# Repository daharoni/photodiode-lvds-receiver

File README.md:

# Photodiode LVDS Receiver

Optical receiver module for the next-generation wireless UCLA Miniscope data
uplink. It succeeds the receiver used with the Miniscope Zero link
(bioRxiv 10.64898/2026.09.05.745822). Target: 50 Mbps line rate (8b/10b,
40 Mbps payload, UI = 20 ns).

Signal chain: silicon APD (primary Hamamatsu S12023-10; FDS010 PIN only as a bench
fallback) on a programmable, temperature-compensated 100-220 V bias
(APD_BIAS) -> OPA857 transimpedance
amplifier -> AC coupling -> OPA855 fixed-gain post-amplifier -> TLV3605
comparator sliced at the AC baseline, LVDS output -> one LVDS pair to an ECP5
FPGA (ULX3S first), which does clock recovery, 8b/10b decode and redundant-lane
merging. An on-module ESP32-C6 trims the APD bias and TIA gain slowly over a
CAN link and reports the module identity. The architecture is analog-first by
decision; see `docs/decision-log.md` (entries 11 and 12).

Each module has one 24-pin USB-C receptacle (decision 14) that carries 5 V, the LVDS
pair duplicated on both SuperSpeed TX pairs, CAN on both RX pairs and USB D+/D- for
programming and self-test from a laptop with no FPGA attached; a scope header and
test points serve the bench. It is intended for a shielded aluminum housing with a
swappable optical bandpass filter.

## Status

Pre-G1, layout in progress (2026-10-12). Rev A schematic is complete (six
hierarchical sheets, 221 components, 144 nets, ERC 0 errors / 0 warnings, spec
revision 4 after decision 14); the generators are frozen and edits go through the
KiCad GUI. The PCB is a 6-layer JLCPCB JLC06161H-3313 board on a 75 x 50 mm
placeholder outline with all 221 footprints placed by the first-pass placement
script; routing is complete (0 unconnected, DRC 11 items accepted in writing in the review README). No hardware, no measurements; three ngspice simulations
with TI models exist (`docs/simulation/README.md`, SIMULATED, not VERIFIED).
Component choices are provisional until the bring-up gates in
`docs/bringup/gates.md` pass. The largest open risks are the APD bias supply, the
USB-C cable and foreign-host behaviour (decision 14), OPA857 behavior at 6 pF,
post-amp clipping and comparator noise at small overdrive, and the firmware
range-control loop. Per-sheet as-built notes with datasheet citations are in
`docs/schematic/`; `docs/receiver-guide.html` is the derived field guide.

## Repo map

| Path | Contents |
|---|---|
| `docs/requirements.md` | Requirements, user answers, open items |
| `docs/architecture.md` | Block-by-block design and reasoning |
| `docs/decision-log.md` | Dated decisions and standing corrections |
| `docs/bringup/gates.md` | Gates G1-G4 and checklists |
| `docs/research/` | Component research; `downloads/` is raw untrusted input |
| `docs/datasheets/` | Datasheets |
| `docs/calculations/` | Design calculations |
| `docs/schematic/` | Rev A sheet specs, per-sheet as-built notes, `overview.html` parts and pinout page |
| `docs/pcb/` | JLCPCB fabrication settings, J50 receptacle DFM note, placement plan |
| `docs/simulation/` | ngspice simulations (OPA855, OPA857 at 6 pF, VCM_REF buffer) |
| `docs/firmware/` | CAN and USB console protocol |
| `docs/receiver-guide.html` | Self-contained field guide derived from the docs above (regenerate when they change) |
| `hardware/pcb/` | KiCad project (`receiver-module/`) |
| `hardware/mechanical/` | Enclosure and filter holder (TBD) |
| `firmware/` | ECP5 gateware; ESP32-C6 module firmware (TBD) |
| `tools/` | Helper scripts |
| `CLAUDE.md` | Guide for Claude Code sessions |

## Opening the KiCad project

Requires KiCad 10 and the lab component library from
`~/Projects/kicad-lab-library`, installed with that repo's install script so
that `${AHARONI_LAB_KICAD_LIB}` resolves. Then open
`hardware/pcb/receiver-module/receiver-module.kicad_pro`. The sheets were
generated by the scripts in `hardware/pcb/receiver-module/gen/` using
`tools/kicad_sch`; the generators are frozen since 2026-10-09 (`gen/FROZEN`,
layout started), so schematic changes go through the KiCad GUI with the spec and
as-built notes in `docs/schematic/` updated by hand.
New parts are added to the lab library by PR, not as project-local symbols.

## Documents to read first

1. `docs/requirements.md`
2. `docs/architecture.md`
3. `docs/decision-log.md`
4. `docs/bringup/gates.md`
5. `docs/receiver-guide.html` (derived overview; open in a browser)

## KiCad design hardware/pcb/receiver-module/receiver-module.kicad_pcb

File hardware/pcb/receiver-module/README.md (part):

# receiver-module (KiCad 10 project, Rev A schematic)

Photodiode LVDS Receiver, Rev A0, Aharoni Lab, UCLA.

**Nothing in this project is fabrication-approved.** The six hierarchical sheets are populated
with lab-library parts, values and footprints per `docs/schematic/rev-a-sheet-specs.md`; project ERC on the root
reports 0 errors and 0 warnings (kicad-cli 10.0.5, 2026-10-09, revision 4 after decision 14). The netlist had 223 components on that date; since 2026-10-22 it has 221 (C181 and R170 removed, Connector 33 -> 31; Power 79, Controller 55, Connector 31 including mounting holes H1-H4 added 2026-10-09, Front End 26, Slicer 17, Monitor 13) on 144 nets. The PCB carries all 221 footprints (H1-H4 included), placed by the first-pass placement script and since hand-placed and fully routed (see Board below). H1-H4 need lab-library PR #62 (branch `add-mounting-holes`, symbol and footprint `MountingHole_2.2mm_M2_Pad_Via`) merged or checked out so the symbol resolves. The S12023 pinout fix (lab-library PR #63) is merged into main. U6 (TLV431, decision 23) needs lab-library branch `add-tlv431` checked out or merged. Status labels used
in notes: VERIFIED / PROPOSED / UNRESOLVED.

## Generated sheets

**FROZEN since 2026-10-09 (PCB layout started).** The generators exit with status 2 while `gen/FROZEN` exists, because regeneration would rewrite the `.kicad_sch` files with new UUIDs and break the schematic-to-board link. Schematic changes now go through the KiCad GUI, with the spec and as-built docs updated by hand. To unfreeze, see `gen/FROZEN` (delete it deliberately, regenerate all sheets in order, re-import to the PCB, re-annotate/re-link footprints). The text below is historical until then.

Each sub-sheet and the root are produced by `gen/<sheet>.py` using the `tools/kicad_sch` package
(`cd tools && python3 gen/...` from the project root; see `tools/kicad_sch/README.md`). Regenerate in
the order power, frontend, slicer, control, connector, controller, root. Each sheet keeps its uuid, so
instance paths stay stable. KiCad's bundled `power:PWR_FLAG` / `power:GND` symbols are used alongside
the lab library. Reference designator ranges per sheet are listed in the spec document.

Validation: `kicad-cli sch erc` and `kicad-cli sch export netlist` on `receiver-module.kicad_sch`
(kicad-cli path in CLAUDE.md). Revision 4 (decision 14) needs lab-library PR #61 (branch `add-usbc-fanout-efuse-esd`: symbols `AharoniLab_Connector:632723300011`, `AharoniLab_Power:TPS259631DDAR`, `AharoniLab_Interface:SN65LVDS104PW`, `AharoniLab_Misc:TPD6E05U06` and their footprints) to be merged before this project is opened on another machine; the generators embed the library symbols, so regenerate after any library change. Revision 3 parts (AharoniLab_Switch / AharoniLab_Switch_SMD for SW60/SW61, lab-library PR #60) are still used: the global sym-lib-table and fp-lib-table must carry those rows.

## How to open

Open `receiver-module.kicad_pro` in KiCad 10. Symbol and footprint libraries come from the global
tables (the lab library is global via `${AHARONI_LAB_KICAD_LIB}`); this project has no
`sym-lib-table` or `fp-lib-table` on purpose. Project text variables: TITLE, REV, COMPANY.

## Sheets

| File | Purpose |
|---|---|
| `receiver-module.kicad_sch` | Root: hierarchical sheet symbols only, in signal-flow order |
| `power.kicad_sch` | VBUS in, TPS259631 eFuse U5 to the internal +5V rail; 3V3 and 3V3_D rails; LT8365 boost + doubler APD bias (HV_ nets, clamp, stage-1 RC filter) -> APD_BIAS, HV_MON divider, DAC_HV trim input, HV_DIS gate |
| `frontend.kicad_sch` | APD, OPA857 TIA with 20k/5k CTRL, AC coupling, OPA855 x7 post-amp, 68 MHz low-pass, AC coupling to SDET_P (TIA_TAP out, VCM_REF in) |
| `slicer.kicad_sch` | TLV3605 sliced at VCM_REF baseline with DAC_TH trim and ~3 mV hysteresis, LVDS out |
| `control.kicad_sch` | Monitor: OPA2320 VCM_REF 1.65 V buffer and BAS70 RSSI minimum detector from TIA_TAP |
| `connector.kicad_sch` | single 24-pin USB-C J50: VBUS out, USB_DP/USB_DN, CC1_SENSE/CC2_SENSE, AUX (SBU tie), LVDS fan-out U50 to both SuperSpeed TX pairs, CAN on both RX pairs (nets CAN_P/CAN_N (CANH/CANL; renamed from CAN_H/CAN_L 2026-10-16 so the KiCad diff-pair router pairs them)), ESD arrays U51/U52, scope header J51, test points |
| `controller.kicad_sch` | ESP32-C6-MINI-1, MCP4728 DAC, ADS1115 ADC, SN65HVD230 CAN, USBLC6 and 22R D+/D- (USB from the Connector sheet), RESET/BOOT switches, CC1_SENSE/CC2_SENSE inputs on IO4/IO5 |

`GND` is a global net (global label in every sub-sheet). Other power nets are sheet pins. Nets at or above 50 V are prefixed `HV_` and, with `APD_BIAS`, belong to net class `HV` (1.0 mm clearance).

## Board

`receiver-module.kicad_pcb`: 6-layer board (stackup below), 75 x 50 mm placeholder outline on Edge.Cuts, all footprints placed by the first-pass placement script (221 components after the shield RC removal, 2026-10-22; 222 components plus the four mounting holes H1-H4 = 225 footprints since R214 was added, 2026-10-23) (below). Routing has been complete since mid-October 2026: 0 unconnected pads, DRC 11 items (2026-10-25; 44 on 2026-10-23, 48 before: the 32 mounting-hole hole_to_hole items went with the H1-H4 `_Pad` footprint variant and the U20 pin 9 starved thermal with a solid connection; remaining 5 silk_edge, 4 diff_pair_gap, 1 uncoupled, 1 silk_overlap), all accepted in writing in `docs/review/2026-10-22-rev-a-review/README.md`; all vias are epoxy filled and capped at order (decision 30). The file holds 225 footprint entries on 2026-10-23 (222 components plus H1-H4). Rules and fabrication settings follow `docs/pcb/jlcpcb-fab-settings.md` (research, PROPOSED values, nothing measured).

### First-pass placement (2026-10-09, PROPOSED)

`tools/pcb_place.py` (runs under KiCad's bundled Python, which has `pcbnew`) applies `placement/placement-spec.json`: board outline, per-block side and region, fixed anchor parts (ICs, connectors, APD, switches, mounting holes) and a `near` pad target for each passive. Passives are packed on a 0.25 mm grid at the nearest free spot to their target, with courtyard-plus-margin collision checks (0.15 mm, 0.65 mm for HV-class parts, 0.3 mm for HV_LADDER), through-hole parts blocking both sides, an ESP32 antenna keep-out, and region growth when a block is full. Blocks are packed in spec order. Result: 223 placed, 0 courtyard overlaps, 0 clearance violations (kicad-cli DRC); remaining DRC items are silk overlaps (reference labels not yet cleaned up), silk near the edge, and the 32 hole-to-hole hits from the via rings of the `MountingHole_2.2mm_M2_Pad_Via` footprints (0.35 mm between the via holes and the 2.2 mm hole, constraint 0.45 mm; swap H1-H4 to the `_Pad` variant without vias or accept it on the high-precision tier).

Run from this directory, with KiCad closed:

```
PYTHONPATH=../../../tools /Users/daharoni/Applications/KiCad/KiCad.app/Contents/Frameworks/Python.framework/Versions/Current/bin/python3 \
  ../../../tools/pcb_place.py receiver-module.kicad_pcb placement/placement-spec.json --out receiver-module.kicad_pcb --report /tmp/report.json
```

It re-places EVERY footprint from the spec, so do not run it on a board with hand placement you want to keep. Floor plan (y down, optical end left): fast chain on the top centre line (D10 at x 9 mm, OPA857, OPA855, filter, TLV3605, SN65LVDS104, ESD arrays, J50 at the right edge with the mouth overhanging 0.95 mm); HV island along the back edge on top (HV_MON, HV_OUT, FB ladder, LT8365 boost, HV_DIS); J51 at the front left; status LED, test points and the RESET/BOOT switches at the front right. Bottom: ESP32-C6 with its antenna over the front edge (keep-out 41-57 x 44-50 mm, both sides), USB ESD and CAN transceiver under J50, CC dividers and eFuse under the connector end, 3V3/3V3_D regulators and DAC/ADC under the HV island, VCM_REF buffer and RSSI detector under the post-amp. The optical window must be centred on the APD can, which sits 1.27 mm from the D10 footprint origin (pad 1, the anode): to the left of it since the 180-degree rotation of 2026-10-22 (see below). The renders used for review are not committed; `kicad-cli pcb render --side top|bottom` regenerates them.

### Hand placement and HV island rearrangement (2026-10-13, PROPOSED)

Daniel re-placed most of the board by hand after the first pass (commit f10238c). The LT8365 island was then rearranged by script (`tools`-free pcbnew snippet, not kept) on the following plan; coordinates are mm from the board's top-left corner, back edge at y = 0. This was the placement state on 2026-10-13, before routing (routing is now complete); nothing was measured.

- U3 is at (48.3, 9.6), rotation 0, so pins 9-16 are on its right side: SW (14, 16) at the top-right corner, FBX (9) at the bottom-right. Power ground leaves the exposed pad at the EN/SW corners, signal ground at the VC/FBX corners (LT8365 Rev. A p.7 pin descriptions, Figure 5 p.16).
- Switching cell along the back edge, right of L1: L1 above U3 with its SW pad 2.4 mm above pin 16, D1 anode 0.6 mm from the L1 SW pad, then R7 and C5 in a row (C5 GND pad to be stitched to GND1 at the pad). C6 (pump) hangs on the same SW blob below D1; D3, D4, C7, R30 continue to the right; C25 sits under the R30 HV_OUT pad. HV_OUT leaves R30 at x 67.3 and is meant to run up to a 0.3 mm lane along the back edge at y about 1.2 (1.0 mm from the edge), then left to the clamp at R17/Q1. Every pad under that lane was placed with its top edge at y >= 2.5 so the 1.0/1.25 mm HV clearances hold.
- FBX island at pin 9: C22 (SS) and R24 (RT) in a column 1.8 mm right of pins 10/11; R8 (ladder end), R12 (bottom resistor) and C26 directly below-right of pin 9 (FBX pads 1.8 mm from the pin); R14 and R15 one column further; the ladder R9, R10, R11 runs right along y 13-15 to the HV_OUT pad of R11 at (63.2, 14.7), 4 mm below D4. R13/C27 (DAC leg) sit beside R14. SYNC parts R26/R27/TP2 (DNP) are in a row at y 17.9: route them only if fitted. C26 (10 pF, DNP in the schematic) is worth fitting as an FBX noise shunt: PROPOSED, not simulated.
- TH1 (NTC in the FBX bottom leg) moved to (10.0, 30.2) just below the APD can, per docs/calculations/apd-bias-design.md section 7 ("on APD can ground tab / thermal link"); its node is the low-impedance end of R12, so the 45 mm run is acceptable.
- LT8365 low-voltage passives in two columns left of U3 (x 40-45): R22/R23 (EN) at the top, C19/C20 at VIN, C21 at INTVCC, R28/R29 at BIAS, R25/C23/C24 at VC; L2 and C18 further left at y 9.9; RV1 at (31, 10.5). J1 moved to x 70.3 and Q3 to (70.5, 15.8) to clear the HV_OUT riser.
- D2 (DNP, purpose not stated in the datasheet) is parked at (66.0, 17.6) off the SW node; if it is ever fitted it must move onto the SW blob.
- Clamp, monitor, stage-1 filter, APD and the whole fast chain are unchanged. DRC (kicad-cli 10.0.5): no clearance, courtyard or hole violations; only silk overlaps (reference labels not yet cleaned up), silk near the edge, and the 32 known mounting-hole via-ring hits.

Distances after the move (centre to centre): C6 pump cap to C87 19 mm (was 10.5), L1 to U20 22.5 mm (was 17.6), FBX end of the ladder (R8) to U3 pin 9 about 2.5 mm (was 16). The D1-R7-C5 path is about 15 mm of trace; with GND1 0.1 mm below F.Cu the loop area stays small provided C5's GND pad and the U3 pad are via-stitched.

Files for the board:

| File | Purpose |
|---|---|
| `receiver-module.kicad_pcb` | board, stackup, plot parameters (`pcbplotparams`) |
| `receiver-module.kicad_pro` | design-rule constraints, net classes and net-class patterns |
| `receiver-module.kicad_dru` | custom DRC rules: diff-pair gap/uncoupled/skew/keep-out, HV edge and pad clearance, same-footprint HV exception. A syntax error makes KiCad ignore the WHOLE file silently (kicad-cli reports no error), so after editing it confirm a rule is live, e.g. delete the last rule and check that DRC messages change |
| `../../../tools/netclass_membership.py` | prints which nets each class pattern catches (run from the repo root) |

### Second placement pass, copper pours and rule areas (2026-10-14, PROPOSED)

Daniel's second hand pass (commit b9dc777) rebuilt the LT8365 cell with D2 (the GND-to-SW clamp of the LT8365 Rev. A p.30 3 V to 6 V reference circuit; purpose still UNRESOLVED in `docs/schematic/power.md`) on the SW node, regrouped the FBX, DAC and pot legs under U3, moved U1/U4 beside the eFuse and Q3/R33/R34/J1 next to the EN divider. Script changes after it (coordinates in mm from the top-left corner):

- Netclass: `Net-(D1-A)` (SW) and `Net-(D1-K)` (replaced by `Net-(D3-A)` on 2026-10-22, see below) added to HV; C22/R24 moved to (51.85, 11.65)/(51.85, 13.25) to clear the 1.25 mm pad rule.
- Hysteresis network: C87 (100 pF) at (37.0, 21.8) on the input side, 2.75 mm from U20 pin 4; R87 swapped with C83 so R87 sits at (42.0, 20.78) on the output side (LVDS_P pad 4 mm from pin 12) and C83 (VCCO 1 uF) moved to (37.0, 17.15).
- ESP32 U60 moved 6 mm left to (43.0, 38.7) with C191/C192 and the ADS1115 cluster (U63 at (28.75, 46.38), R206/R207/C197/C198/C200 at x 23.8, C195 at (29.0, 48.75), R208/C199/R209 at x 33.75). TP62/TP63/R203/D60 moved out of the antenna end to x 51 to 54, y 36 to 40.
- J51 (debug header) now lies along the front edge at (54.31, 47.6), rotation 90, pins at y 47.6 from x 54.3 to 67.0, 2.9 mm right of the antenna keep-out and clear of H4. The USB-C CC network (C182, C183, R181, R184, R185, R187, R188, R189) that was under it moved to B.Cu columns x 52.5 and 55.5, y 35.0 to 39.8, between the module and U64.
- Zones (all `thermal relief` pad connection, clearance 0.2 mm, min width 0.2 mm, spoke 0.4 mm, gap 0.25 mm, islands removed): `GND_F` (F.Cu), `GND1` (In1.Cu), `GND_In3` (In3.Cu, priority 0), `GND2` (In4.Cu), `GND_B` (B.Cu), each the full outline. Rail pours on In3.Cu with higher priority (reshaped 2026-10-15 against the pad list, PROPOSED): `PWR_3V3` (priority 1: U1-output corner x 54-72, y 1.5-9.5, neck x 52-58.8 down to y 20.4, front-end band x 6-49, y 17.5-31.8), `PWR_3V3_D` (priority 2: x 49.4-72 from y 20.8, so the DAC cluster U62/C194/R192 at x 50.8-51.8 is inside, and the front band x 18-72, y 32.3-49.5), `PWR_5V` (priority 3: U1-input column x 57.5-62.3, y 3.3-18 plus the eFuse/U4-input block x 62.3-72, y 9.9-18; it cuts the 3V3 pour, which keeps a 1.8 mm strip along y 1.5-3.3). Rail pads that stay outside their pour and need a trace: 3V3 TP50; 3V3_D R33 (EN divider), R39 (at J50) and the U4 output group U4.5/C30/C31 (link on B.Cu plus one In2 track down to the 3V3_D pour); +5V C18/L2 (LT8365 input, In2 track from the 5V pour, about 21 mm) and C29. The user's first-pass 3V3/3V3_D/+5V outer-layer tracks can be replaced by vias into these pours. In2.Cu has no pour (signal layer). The three rail zones report `isolated_copper` until their vias exist. U10 pad 17 (OPA857 exposed pad) has a per-pad solid zone connection because the input window below leaves it one spoke.
- Rule areas (all six copper layers): `ANT_KEEPOUT` x 35.35-50.65, y 44.2-50 (no fills, tracks, vias or pads; the module body is 13.2 x 16.6 mm with the antenna at the front end, MINI-1 datasheet v1.5 Fig. 10-1; the lateral/forward clearance Espressif recommends was not read, so the 1 mm side margin and the 2.9 mm gap to J51 are UNRESOLVED, check `docs/datasheets/esp32-c6-hw-design-guidelines.pdf`). The module sits mid-edge, not at a corner. The radio is unused on Rev A (CAN and USB only, decisions 11 and 12), so the mid-edge placement is accepted (PROPOSED); the keep-out stays as drawn. `TIA_IN_WINDOW` x 10.5-15.9, y 24.0-26.1 (no fills only): the plane window under the APD anode pad, the TIA_IN trace and OPA857 pins 15/16, per SBOS630D section 10.1 (a) and Figure 48 p.24 (VERIFIED guidance, PROPOSED size). `OPA855_IN_WINDOW` x 24.85-27.5, y 20.4-24.35 and `OPA855_OUT_WINDOW` x 25.6-27.0, y 25.6-27.8 (no fills only, added 2026-10-22, decision 27): the windows under the OPA855 input pins with R53/R54 and under its output pin, per SBOS622D 9.4.1 and Fig. 9-12 (guidance VERIFIED in the review, sizes PROPOSED). No plane cut-outs under the HV copper: planes stay solid there on purpose (0.0994 mm prepreg, 220 V, see the HV routing notes above); the earlier idea of an all-layer keep-out around the HV island in `docs/pcb/jlcpcb-fab-settings.md` section 3 is withdrawn.
- DRC after this: no clearance, courtyard or keep-out violations; remaining items are 3 `isolated_copper` (rail zones, unrouted), silk, and the 32 hole-ring warnings (state on 2026-10-14, before routing).
- Reference designators (2026-10-14): all 223 (then; 221 now) moved off the silkscreen to F.Fab/B.Fab, 0.5 mm text centred on each courtyard, so the silk carries only footprint graphics (outlines, pin-1/polarity marks) and the Fab layers are the assembly drawing. The footprints' own `${REFERENCE}` Fab texts are hidden on the board to avoid doubles. Silk DRC items dropped from 320 to 7 (J50/U60 outlines at the edge, U62 polygon under mask, U51/U52 outlines touching). Fab layers are not in the Gerber set; plot them to PDF for assembly.
- J50 shield (2026-10-22, Daniel, PROPOSED): C181 (1 nF) and R170 (1 M, DNP) deleted; the eight S1 pads (four shell posts) are on net GND (`/Connector/SHIELD` no longer exists). Each shell post pad connects solid to the GND pour and planes on every layer (decision 16 as reworded 2026-10-22; the plated barrels tie the planes, no extra vias), with the housing bonded at the connector end. The zones were not refilled in the saved file: refill them (KiCad Fill All Zones, or `kicad-cli pcb drc --refill-zones` on a copy) before judging DRC; on a refilled copy the S1 pads connect to the GND pours with 0 unconnected S1 items.
- U51 CAN channels swapped (2026-10-22, Daniel, GUI, routing only): pin 9 (and stacked NC pin 6) = CAN_P (J50 B11), pin 8 (and NC pin 7) = CAN_N (J50 B10); electrically neutral, U52 unchanged.
- D10 APD pinout corrected (2026-10-22, design review B1, VERIFIED against KAPD1007E19 p.4 outline KAPDA0136EC): the lab-library S12023-10 symbol had pin 1 = K and pin 3 = A; the Hamamatsu pin diagram (bottom view) draws the diode between terminals 3 and 1 with the bar on the 3 side, so pin 1 = anode, pin 3 = cathode. As wired before the fix, HV_K sat on the physical anode and the APD would have conducted forward through R19 + R50 into the OPA857 IN pin. Fix: symbol pin numbers swapped in the library (branch `fix-s12023-pinout`) and in the embedded copy in frontend.kicad_sch; on the board D10 was rotated 180 degrees about the can axis (footprint origin now at (11.54, 25.0), rotation 180) so pad 1 (anode, TIA_IN) stays at (11.54, 25.0) next to U10 and pad 3 (cathode, HV_K) at (9.0, 25.0); the HV_K and TIA_IN tracks are unchanged and the case pad 2 moved from below to above the can axis. The index tab of the fitted part therefore points to the lower right (toward U10); the F.Fab tab outline shows this. Zones refilled, ERC 0/0, netlist differs from before only at D10 pins 1/3, DRC unchanged (52 items, 0 unconnected). Footprint pad geometry unchanged (its description already mirrors the bottom view correctly); only its description text was corrected.
- D10 pads reduced to 1.0 mm (2026-10-22, design review P1, decision 25; lab-library PR #65, branch `s12023-1mm-pads`, needed checked out or merged for the library to match the board): pad 1 square, pads 2 and 3 round, drill 0.7 mm unchanged, annular ring 0.15 mm (JLCPCB standard-tier minimum, 0.20 recommended). Done by text edit with KiCad closed; the board copy of the footprint carries the new sizes and description. Measured copper gaps from the cathode pad 3 (HV_K, 220 V), pcbnew shape distances: case pad 2 (GND) 0.80 mm (was 0.60), anode pad 1 (TIA_IN) 1.54 mm (was 1.34), anode corner to case 0.59 mm (was 0.35, low voltage); GND/3V3 zones on all six layers 1.00 mm; TIA_IN track 1.97 mm. The `hv same footprint pads` DRC exception hides the first two gaps, so the waiver is written into the .kicad_dru comment and the assembly rule (clean and conformal-coat the solder side at D10) is in gates.md G4. Zones refilled; DRC 52 (unchanged), 0 unconnected, parity clean.
- C50 moved to the cathode, R50 and C8 follow (2026-10-22, design review P2, decision 26; script with KiCad closed). The filter column now sits on the empty strip left of D10 at x 4.60: C8 at (4.60, 13.60) rot 90 (APD_BIAS pad at y 15.08 below, GND pad at y 12.12 above with its via moved to (5.60, 12.40) to clear the HV_MON track on B.Cu), R50 at (4.60, 18.50) rot 270 (APD_BIAS pad at y 17.04, HV_K pad at y 19.96), C50 at (4.60, 24.00) rot 90 (GND pad at y 22.53 with two vias at x 4.20 and 5.00, HV_K pad at y 25.47 facing the cathode). HV_K leaves D10 pad 3 radially along y 25 to x 7.30 and into C50's pad (4.59 mm of trace, pad centres 4.43 mm apart; was 6.78 mm), and a second run from C50's pad corner up x 7.30 to R50's HV_K pad (1.20 mm from C50's GND pad, netclass 1.0). Under the 2.7 mm flange: 0.93 mm of track plus the pad (was 1.65 mm plus the pad). APD_BIAS from the island now runs down x 7.70 to y 13.5, then diagonally into C8's pad and straight to R50. The old stubs and the two old GND vias are gone. HV pad rule (1.25 mm) nearest other-net copper: R50.2 to C50's GND pad 1.43 mm, the rest 1.80 mm. DRC 52 (unchanged, no new items), 0 unconnected, parity clean, ERC 0/0. D10 gets a 1.5 mm insulating TO-18 spacer at assembly (decision 26; part UNRESOLVED).
- OPA855 cell re-laid out (2026-10-22, design review P3, decision 27; script with KiCad closed). U11 at (26.12, 25.00) rotated to 270 degrees: pins 4/3/2/1 (IN+, IN-, NC, FB) along the top edge at y 24.05, x 25.37 to 26.87; pins 5/6/7/8 (GND, OUT, 3V3, PD) along the bottom at y 25.95. R53/R54 unchanged; FB now a 1.38 mm straight track to R53 pad 2, IN- 3.15 mm in total (pin 3 to R53 pad 1 and on to R54), IN+ 4.65 mm to C51. R56 vertical at (26.40, 28.10) rot 270 (OUT pad at y 27.28, LPF_OUT pad at y 28.93), C54 at (28.80, 28.93) rot 0 (LPF_OUT pad left, GND pad right with an in-pad via), C52 at (28.20, 27.10) rot 180 (3V3 pad right at x 28.68 with a 3V3 via at (29.60, 26.00); GND pad left at x 27.72, solid zone connection, via at (27.72, 27.60) kept 0.3 mm from the RSSI_HOLD In2 track that runs along y 27.10), TP10 at (30.50, 27.40) on the LPF_OUT run (R56 pad 2 -> C54 pad 1 -> y 28.1 -> x 30.5 up to the existing track at y 25.28). GND via for pin 5 at (24.45, 26.00) (the B.Cu U30 column at x 24.9-25.8 leaves no room nearer). New rule areas (no copper pour, all six layers): OPA855_IN_WINDOW x 24.85-27.5, y 20.4-24.35 and OPA855_OUT_WINDOW x 25.6-27.0, y 25.6-27.8 (SBOS622D 9.4.1, Fig. 9-12). The 24 old tracks of the cell were deleted and redrawn. DRC 52 (no new items), 0 unconnected, parity clean, ERC 0/0.
- Ground-return vias (2026-10-22, design review P5/P7/P8, decision 28; checked placer script, KiCad closed): C5 GND pad 3 vias (was 1), U3 EP 5 vias (was 2; left column only, the HV pad rule from U3 pads 14/16 blocks x > 47.2), all J50 S1 pads solid zone connection (no stitching vias: the plated posts already tie every layer, decision 16 reworded), vias at U50 pin 8, C56 and C57. Still without a nearby GND via (no legal spot within about 2 mm, see decision 28): U50 pin 5, C184, C185, U51 pin 5, U52 pins 5/10, U4 pin 2, C30, C31, C196, C1, U62 pin 10. DRC 48 (the four J50 starved-thermal items gone), 0 unconnected, parity clean.
- R7 moved into the pump-charge branch (2026-10-22, design review S1, decision 18): D1 cathode now goes straight to HV_V1 and R7 20R sits between HV_V1 and the D3 anode (net `Net-(D3-A)`, in the HV netclass in place of `Net-(D1-K)`), as LT8365 Rev. A p.30 (R8) and DC2838A REV02 (R10). Board (Daniel, GUI, commit 40262da): R7 vertical at (56.83, 5.83) with pad 2 (HV_V1) at the top, D1 K to C5 pad 1 along y 4.8-6.05, C5 moved to (61.00, 4.90), C7 to (61.38, 10.48) with its HV_V1 feed from C5 pad 1; D3 and D4 unchanged. DRC after the change (56 items, 0 unconnected, parity clean): four new 'hv pad clearance' (1.25 mm) items still to be cleared by a move: +5V via at (60.97, 4.05) to C5 pad 1 0.67 mm; 3V3_D via at (63.25, 13.23) to C7 pad 2 1.08 mm; D3 pad 2 (Net-(D3-A)) to C7 pad 1 1.10 mm; R7 pad 1 to D3 pad 1 (HV_PUMP) 1.05 mm. Side effect undone the same day: the 'Update Symbols from Library' run had reset the 27 test-point Footprint fields to the library default `TestPoint_Plated_Hole_D1.0mm_interconnect`, and Update PCB from Schematic then swapped the 27 SMD test points for 1.0 mm plated holes (0.5 mm drill), adding 85 DRC items (holes against vias, shorts, mask bridges). Fields and footprints are back on `TestPoint_Pad_1.0x1.0mm_interconnect` (the embedded library copy keeps the plated-hole default, as the library does); when updating symbols from the library, untick the Footprint field under 'Update/reset fields' or the test points flip again. Vias were never affected: 209, all 0.45/0.25.
- R17, R18, R20, R32 changed from 0603 to 0805 (2026-10-22, review S5a, decision 22, value text `4.99M 1% 0805 150V`, Yageo RC0805 spec V0 p.3: 150 V working). Done by script with KiCad closed: library footprint `R_0805_2012Metric_N` substituted in place with position, rotation, fields, path and pad nets carried over; the existing track ends fall inside the larger pads, so no track was redrawn. Re-placement to clear courtyards: C28 moved 0.3 mm left (to x 14.98) together with the HV_MON via under its pad 1 and the three track ends on them; R20 moved 0.2 mm right (to x 21.92); R32 moved 0.25 mm up (to y 10.09). R17/R18 top pad edges stay at y 2.70, 1.40 mm below the HV_OUT lane. Zones refilled; DRC 52 (unchanged), 0 unconnected, parity clean; ERC 0/0.
- OVP limiter added (2026-10-22, decision 23, by script with KiCad closed): R21 rotated to 0 so pad 1 (HV_MON) is at (14.43, 11.92) and pad 2 (new net `/Power/OVP_REF`) at (16.08, 11.92); the old GND via and stubs at its pad 2 removed and the HV_MON feed from C28 pad 1 re-drawn to (14.43, 11.92). R45 54.9k 0603 at (15.25, 13.60) rot 180: pad 1 OVP_REF (16.08, 13.60), pad 2 GND (14.43, 13.60) with a new GND via in the pad; tap track vertical at x 16.08. U6 TLV431 SOT-23 at (18.90, 14.50) rot 0: REF (17.96, 13.55) to the tap, anode (19.84, 14.50) to a new GND via at (20.60, 14.50), cathode (17.96, 15.45) to EN on F.Cu: along y 15.45 to x 29.55, to (31.0, 14.0), up x 31.0 to y 10.6, then to the Q3 drain pad at (33.66, 9.37); 0.15 mm, no via, passes 0.9 mm left of the Q3/C18 courtyards. Values R21 45.3k, R22/R23 20k on the footprints. Zones refilled; ERC 0/0, DRC 52 (unchanged), 0 unconnected, parity clean. Lab library branch `add-tlv431` (AharoniLab_Power:TLV431) must be checked out or merged for U6 to resolve.
- Q4 Darlington driver added (2026-10-22, decision 24, by script with KiCad closed): Q4 MMBTA42 SOT-23 at (23.60, 6.73) rot 0 right of Q1 (pads 1 B Net-(Q2-C) at (22.66, 5.78), 2 E Net-(Q1-B) at (22.66, 7.68), 3 C HV_OUT at (24.54, 6.73)). HV_OUT now runs from Q1 pad 3 along y 6.73 through Q4's pad gap to Q4 pad 3, then (25.30, 7.49)-(25.30, 9.30)-(24.22, 10.38) into R20 pad 1; the old diagonal (19.68, 6.73)-(22.55, 9.60) is gone. The 10 M node (R18 pad 2, Q2 collector, now net Net-(Q2-C), added to the HV class) keeps its SIG_IN run from the via at (14.05, 3.40) and continues on SIG_IN via (16.13, 4.20) to a new via at (22.66, 4.20) under Q4's base; the old SIG_IN leg to (17.53, 5.60) was removed. Q4's emitter goes by F.Cu to a new via at (21.30, 8.40), then SIG_IN via (18.50, 5.60) to the existing via at (17.53, 5.60) and the F.Cu stub into Q1's base pad (net Net-(Q1-B), now Q4 E to Q1 B only). Q4 added to the "hv escape inside own courtyard" rule in the .kicad_dru. HV-class vias: Net-(Q2-C) 3, Net-(Q1-B) 2 (review P4 still open). Zones refilled; ERC 0/0, DRC 52 (unchanged), 0 unconnected, parity clean.
- R214 and cleanups (2026-10-23, decision 32, hand edit with KiCad closed, PROPOSED): R214 2.2k 0603 placed on F.Cu at (44.0, 34.6) doc coordinates, over the ESP32 module (which is on B.Cu), in the F.Cu TIA_CTRL run along y 35.25 with 45 degree jogs to its pads. The U60-side stub, via (48.0, 35.25) and track now carry Net-(U60-GPIO20); R214 pin 1 is on /TIA_CTRL. Footprint Value fields updated to match the schematic (R53/R54 0.1 %, C50 500V C0G, R50 200V, C54/C87 C0G, R1 18.7k, R199 91k); D2 DNP cleared, C200 DNP set. Removed: dangling vias on VCM_REF (23.725, 27.81) and TIA_CTRL (16.475, 30.775), two sub-0.06 mm EN stubs, and one of the two co-located GND vias at (52.65, 11.7). Result: ERC 0/0; DRC 44 items (32 mounting-hole hole_to_hole, 5 silk_edge, 4 diff_pair_gap, 1 starved_thermal, 1 uncoupled, 1 silk_overlap), 0 unconnected; schematic parity 199 field-mismatch notes (normal).
- Mounting holes and DRC close-out (2026-10-25, decision 33, pcbnew script with KiCad closed, PROPOSED): H1-H4 swapped to `AharoniLab_Connector:MountingHole_2.2mm_M2_Pad` (plated pad, no via ring; same positions, GND, schematic footprint fields updated in connector.kicad_sch, instance paths kept so parity stays clean); U20 pad 9 set to a solid zone connection. DRC 11 items (5 silk_edge, 4 diff_pair_gap, 1 uncoupled, 1 silk_overlap), all accepted in writing in the review README DRC table; 0 unconnected; ERC 0/0; parity 199 field notes. Open copper work for Daniel: a bottom-side +5V pour from the eFuse output to the U1/U4/L2 inputs replacing the 0.15 mm necks plus a second via onto the In3 +5V zone; the five 0.15 mm pieces of 5V_HVIN widened to 0.5 mm; the SW node (Net-(D1-A)) kept small at 0.5 mm with C5 moved next to D1 (hot loop), not poured; left-edge GND stitching.
- D50 VBUS TVS parked (2026-10-25, decision 34, pcbnew script with KiCad closed, PROPOSED): `AharoniLab_Diode_SMD:D_SOD-123F` (SMF5.0A) added on F.Cu at (71.55, 17.17) doc coordinates, rotated 90, next to the VBUS entry; pad 1 VBUS, pad 2 GND; unrouted by intent, Daniel places and routes it (its cathode pad currently sits on the VBUS via at (71.35, 18.58), so DRC reports 0 unconnected). The footprint comes from the lab library branch `add-smf5.0a` (PR #66); `${AHARONI_LAB_KICAD_LIB}` must point at a checkout that has it (main after the merge). Footprint count 226 (223 components plus H1-H4). DRC 11, parity 199 field notes, ERC 0/0.

## Fabrication settings (JLCPCB, 6 layers) - PROPOSED

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
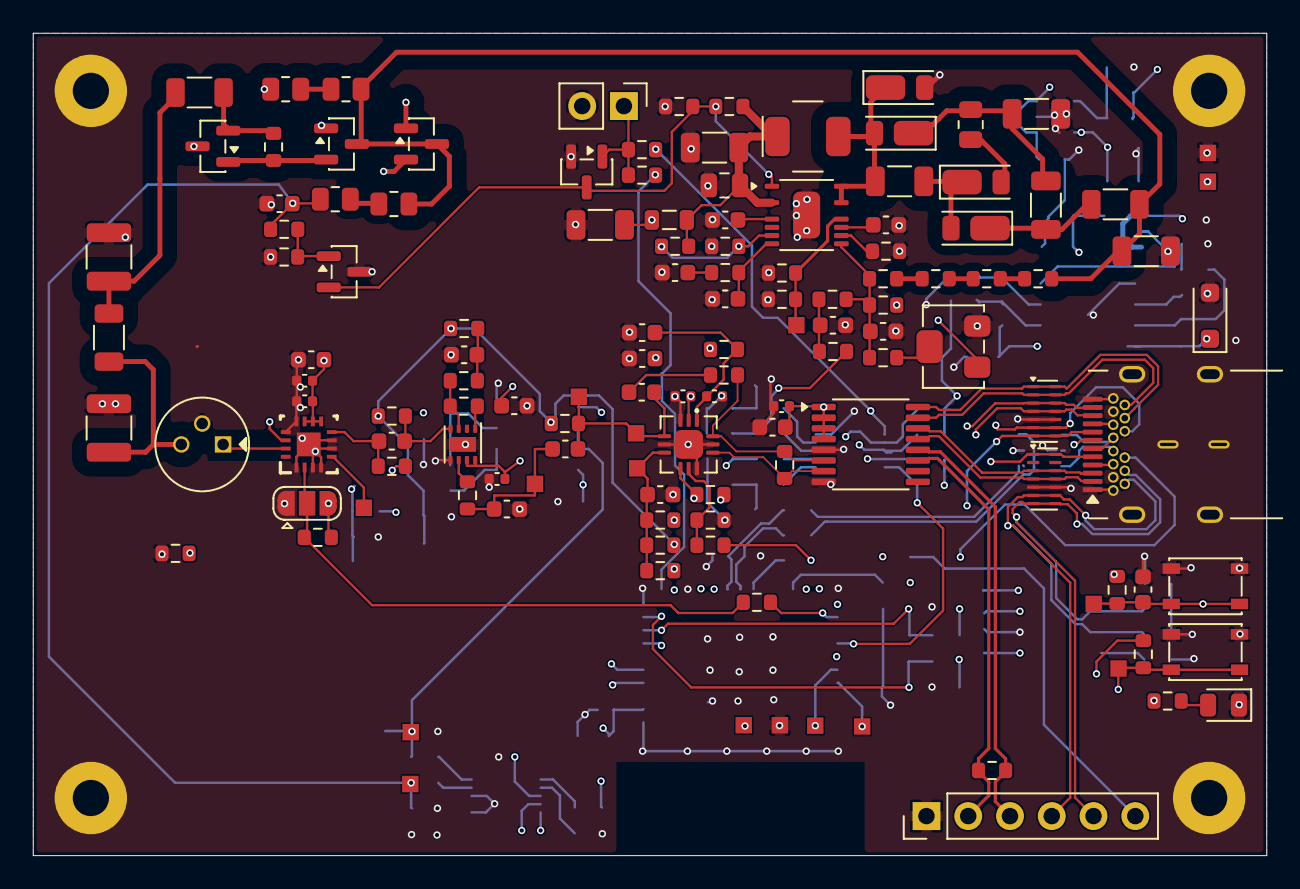
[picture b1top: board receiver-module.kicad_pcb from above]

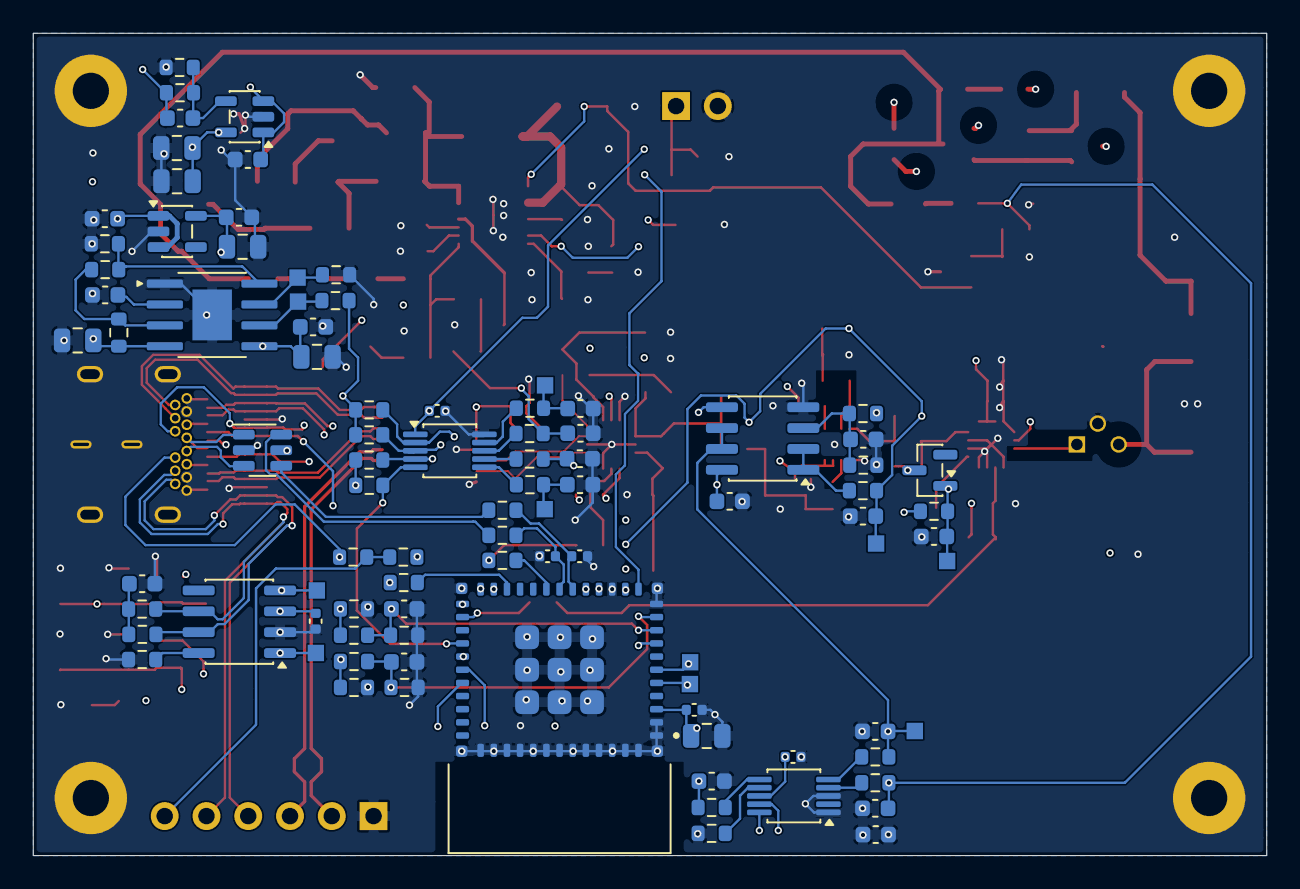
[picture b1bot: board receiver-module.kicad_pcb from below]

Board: 6 copper layers, 75.0 x 50.0 mm, 226 parts (92 on the bottom side), 121 nets.

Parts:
C1, C30: 10uF 10V; C_0805_2012Metric_N
C2, C27, C182, C183: 100nF; C_0603_1608Metric_N
C5, C6, C7: 0.1uF 200V X7R; C_1206_3216Metric_N
C8, C50: 10nF 500V C0G; C_1210_3225Metric_N
C9, C185: 1uF; C_0603_1608Metric_N
C10, C11: 4.7uF 10V; C_0805_2012Metric_N
C12, C23: 1nF C0G; C_0603_1608Metric_N
C18, C19: 10uF 50V; C_1206_3216Metric_N
C20: 4.7uF 50V; C_0805_2012Metric_N
C21: 1uF 25V; C_0603_1608Metric_N
C22: 0.22uF; C_0603_1608Metric_N
C24, C26: 10pF C0G; C_0603_1608Metric_N
C25: 1nF 500V; C_1206_3216Metric_N
C28: 10nF; C_0603_1608Metric_N
C29, C31: 1uF 10V; C_0603_1608Metric_N
C32: 47nF X7R 10V; C_0603_1608Metric_N
C33: 4.7uF 25V; C_0805_2012Metric_N
C51, C55, C100, C103, C201, C202, C203, C204: 100n; C_0603_1608Metric_N
C52, C56, C57, C80, C82, C192, C194, C195, C196: 100n; C_0402_1005Metric_N
C53, C58, C59, C81, C83, C101, C190: 1u; C_0603_1608Metric_N
C54: 47pF C0G; C_0603_1608Metric_N
C84, C197, C198, C199, C200: 10n; C_0603_1608Metric_N
C87: 100pF C0G; C_0603_1608Metric_N
C102: 1n C0G; C_0603_1608Metric_N
C180: 4.7nF; C_0603_1608Metric_N
C184: 100nF; C_0402_1005Metric_N
C191: 10u; C_0805_2012Metric_N
C206, C207: TBD; C_0402_1005Metric_N
D1, D2, D3, D4: DFLS1150-7; Diodes_PowerDI-123
D10: S12023-10; Hamamatsu_S12023_TO-18_P2.54mm_Vertical
D30: BAS70; SOT-23
D50: SMF5.0A; D_SOD-123F
D60: LED; LED_0805_2012Metric
H1, H2, H3, H4: MountingHole_Pad; MountingHole_2.2mm_M2_Pad
J1: HV FORCE ON; PinHeader_1x02_P2.54mm_Vertical
J50: 632723300011; Wuerth_632723300011
J51: DEBUG / scope; PinHeader_1x06_P2.54mm_Vertical
JP10: 3V3=20k; SolderJumper-3_P1.3mm_Open_RoundedPad1.0x1.5mm
L1: 10uH 1.5A; Wuerth_74437324100
L2: 0.47uH 2.1A; L_0805_2012Metric_N
Q1, Q4: MMBTA42; SOT-23
Q2: MMBT3904; SOT-23
Q3: DMN2056U-7; SOT-23
R1: 18.7k 1%; R_0603_1608Metric_N
R2: 10.0k 1%; R_0603_1608Metric_N
R7: 20R; R_0805_2012Metric_N
R8, R9, R10, R11: 2.05M 1%; R_0603_1608Metric_N
R12: 86.6k 1%; R_0603_1608Metric_N
R13, R81, R86, R100, R101, R190, R191, R192, R197, R198, R206, R207, R208, R209: 10k; R_0603_1608Metric_N
R14: 150k 0.1%; R_0603_1608Metric_N
R15, R103: 1M; R_0603_1608Metric_N
R16: 4.02k 1%; R_0603_1608Metric_N
R17, R18, R20, R32: 4.99M 1% 0805 150V; R_0805_2012Metric_N
R19: 27k 1206 200V; R_1206_3216Metric_N
R21: 45.3k 1%; R_0603_1608Metric_N
R22, R23: 20k 1%; R_0603_1608Metric_N
R24, R25: 84.5k 1%; R_0603_1608Metric_N
R26, R33, R39, R57, R85, R185, R187, R188, R189: 100k; R_0603_1608Metric_N
R27, R28, R29, R80, R83, R205: 0R; R_0603_1608Metric_N
R30: 47R; R_1206_3216Metric_N
R34, R51, R58, R59, R84, R186, R203, R204: 1k; R_0603_1608Metric_N
R35: 357k 1%; R_0603_1608Metric_N
R36: 43.2k 1%; R_0603_1608Metric_N
R37: 100k 1%; R_0603_1608Metric_N
R38: 1.21k 1%; R_0603_1608Metric_N
R45: 54.9k 1%; R_0603_1608Metric_N
R50: 10k 200V; R_1206_3216Metric_N
R53: 301 0.1%; R_0603_1608Metric_N
R54: 49.9 0.1%; R_0603_1608Metric_N
R56: 49.9; R_0603_1608Metric_N
R60, R102: 10; R_0603_1608Metric_N
R82: 150k; R_0603_1608Metric_N
R87: 5.49k; R_0603_1608Metric_N
R177, R210, R211, R212, R213: 100R; R_0603_1608Metric_N
R180: 100R 0.1%; R_0603_1608Metric_N
R181, R184: 5.1k 1%; R_0603_1608Metric_N
R182, R183: 60.4R 1%; R_0603_1608Metric_N
R193, R194: 22R; R_0603_1608Metric_N
R195, R196: 4.7k; R_0603_1608Metric_N
R199: 91k; R_0603_1608Metric_N
R214: 2.2k; R_0603_1608Metric_N
RV1: 50k trim; Bourns_3224W_SMD
SW60: RESET; SW_SPST_PTS810
SW61: BOOT; SW_SPST_PTS810
TH1: NTC 10k B3950; R_0603_1608Metric_N
TP2: SYNC_EXT; TestPoint_Pad_1.0x1.0mm_interconnect
TP3: IMON; TestPoint_Pad_1.0x1.0mm_interconnect
TP4: FLT; TestPoint_Pad_1.0x1.0mm_interconnect
TP10: PA_OUT; TestPoint_Pad_1.0x1.0mm_interconnect
TP11, TP21: SDET_P; TestPoint_Pad_1.0x1.0mm_interconnect
TP12: TIA_REF; TestPoint_Pad_1.0x1.0mm_interconnect
TP20: SDET_N; TestPoint_Pad_1.0x1.0mm_interconnect
TP30: VCM_REF; TestPoint_Pad_1.0x1.0mm_interconnect
TP31, TP52: RSSI; TestPoint_Pad_1.0x1.0mm_interconnect
TP32: RSSI_HOLD; TestPoint_Pad_1.0x1.0mm_interconnect
TP50: 3V3; TestPoint_Pad_1.0x1.0mm_interconnect
TP51: 3V3_D; TestPoint_Pad_1.0x1.0mm_interconnect
TP53: HV_MON; TestPoint_Pad_1.0x1.0mm_interconnect
TP54, TP55: GND; TestPoint_Pad_1.0x1.0mm_interconnect
TP60: EN; TestPoint_Pad_1.0x1.0mm_interconnect
TP61: BOOT; TestPoint_Pad_1.0x1.0mm_interconnect
TP62: TXD0; TestPoint_Pad_1.0x1.0mm_interconnect
TP63: RXD0; TestPoint_Pad_1.0x1.0mm_interconnect
TP64: SDA; TestPoint_Pad_1.0x1.0mm_interconnect
TP65: SCL; TestPoint_Pad_1.0x1.0mm_interconnect
TP66: CAN_TX; TestPoint_Pad_1.0x1.0mm_interconnect
TP67: CAN_RX; TestPoint_Pad_1.0x1.0mm_interconnect
TP68: DAC_A; TestPoint_Pad_1.0x1.0mm_interconnect
TP69: DAC_D; TestPoint_Pad_1.0x1.0mm_interconnect
U1: TPS79901DDCT; SOT-23-5
U3: LT8365EMSE; Analog_MSE16-12_MSOP-16-1EP_3x4mm_P0.5mm_EP1.65x2.85mm
U4: TPS7A2033PDBV; SOT-23-5
U5: TPS259631DDAR; Texas_DDA-R-PDSO-G8_SO-PowerPAD-8_3.9x4.9mm_P1.27mm_EP2.4x3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
U6: TLV431; SOT-23
U10: OPA857; RGT0016A
U11: OPA855IDSGR; Texas_DSG0008A_WSON-8_2x2mm_P0.5mm_EP0.9x1.6mm
U20: TLV3605RVKR; Texas_RVK0012A_WQFN-12-1EP_3x3mm_P0.5mm_EP1.75x1.75mm
U30: OPA2320AIDR; SOIC-8_3.9x4.9mm_P1.27mm
U50: SN65LVDS104PW; TSSOP-16_4.4x5mm_P0.65mm
U51, U52: TPD6E05U06; Texas_R-PUSON-N14
U60: ESP32-C6-MINI-1-N4; Espressif_ESP32-C6-MINI-1
U61: USBLC6-2SC6; SOT-23-6
U62: MCP4728T-E_UN; MSOP-10_3x3mm_P0.5mm
U63: ADS1115IDGSR; MSOP-10_3x3mm_P0.5mm
U64: SN65HVD230D; SOIC-8_3.9x4.9mm_P1.27mm

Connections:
/3V3: C10.1, C11.1, C12.1, C52.1, C56.1, C57.1, C58.1, C59.1, C80.1, C81.1, C103.1, C184.1, C185.1, JP10.3 (B), R1.1, R57.1, R80.1, R81.2, R100.1, R103.2, RV1.1, TP50.1 (1_1), U1.5 (OUT), U10.9 (VS+), U10.10 (VS+), U10.11 (VS+), U10.14 (TEST_IN_VS+), U11.7 (VS+), U11.8 (PD), U20.2 (VCCI), U30.8 (V+), U50.1 (EN1), U50.2 (EN2), U50.3 (EN3), U50.4 (VCC)
/3V3_D: C30.1, C31.1, C191.2, C192.2, C194.1, C195.1, C196.2, R33.1, R39.1, R190.1, R191.1, R192.1, R195.1, R196.1, R197.1, R198.1, TP51.1 (1_1), U4.5 (OUT), U60.3 (3V3), U62.1 (VDD), U63.8 (VDD), U64.3 (VCC)
/APD_BIAS: C8.1, R19.2, R50.1
/AUX: J51.6, R186.2, R204.2
/CAN_N: J50.A10 (SSRXN2), J50.B10 (SSRXN1), J51.5, R183.2, U51.7 (D3-), U51.8 (D3-), U52.4 (D2-), U52.11 (D2-), U64.6 (CANL)
/CAN_P: J50.A11 (SSRXP2), J50.B11 (SSRXP1), J51.4, R182.1, U51.6 (D3+), U51.9 (D3+), U52.3 (D2+), U52.12 (D2+), U64.7 (CANH)
/CC1_SENSE: C182.1, R185.2, R187.1, U60.9 (GPIO4)
/CC2_SENSE: C183.1, R188.2, R189.1, U60.10 (GPIO5)
/Connector/AUX_CAB: J50.A8 (SBU1), J50.B8 (SBU2), R186.1, U52.7 (D3-), U52.8 (D3-)
/Connector/CC1: J50.A5 (CC1), R181.1, R185.1, U51.1 (D1+), U51.14 (D1+)
/Connector/CC2: J50.B5 (CC2), R184.1, R188.1, U52.6 (D3+), U52.9 (D3+)
/Connector/LVDS_DBG_N: J51.2, R177.2, U50.11 (3Z)
/Connector/LVDS_DBG_P: J51.3, R177.1, U50.12 (3Y)
/Connector/LVDS_OUT1_N: J50.B2 (SSTXP2), U50.15 (1Z), U52.2 (D1-), U52.13 (D1-)
/Connector/LVDS_OUT1_P: J50.B3 (SSTXN2), U50.16 (1Y), U52.1 (D1+), U52.14 (D1+)
/Connector/LVDS_OUT2_N: J50.A2 (SSTXP1), U50.13 (2Z), U51.4 (D2-), U51.11 (D2-)
/Connector/LVDS_OUT2_P: J50.A3 (SSTXN1), U50.14 (2Y), U51.3 (D2+), U51.12 (D2+)
/Controller/ADC_AIN0: R206.1, U63.4 (AIN0)
/Controller/ADC_AIN1: R207.1, U63.5 (AIN1)
/Controller/ADC_AIN2: R208.1, U63.6 (AIN2)
/Controller/ADC_AIN3: R209.1, U63.7 (AIN3)
/Controller/BOOT: R191.2, SW61.2, TP61.1 (1_1), U60.23 (GPIO9)
/Controller/CAN_RX: TP67.1 (1_1), U60.24 (GPIO18), U64.4 (R)
/Controller/CAN_TX: TP66.1 (1_1), U60.25 (GPIO19), U64.1 (D)
/Controller/DACO_A: R210.1, U62.6 (OUTA)
/Controller/DACO_B: R211.1, U62.7 (OUTB)
/Controller/DACO_C: R212.1, U62.8 (OUTC)
/Controller/DACO_D: R213.1, U62.9 (OUTD)
/Controller/DAC_A: C201.1, R210.2, TP68.1 (1_1)
/Controller/DAC_D: C204.1, R213.2, TP69.1 (1_1)
/Controller/DAC_RDY: R198.2, U60.28 (GPIO22), U62.5 (RDY/~BSY)
/Controller/EN: C190.1, R190.2, SW60.2, TP60.1 (1_1), U60.8 (EN)
/Controller/GPIO8: R192.2, U60.22 (GPIO8)
/Controller/LDAC: R197.2, U60.15 (GPIO6), U62.4 (~LDAC)
/Controller/LE_HYS_E: R205.2, U60.19 (GPIO14)
/Controller/RXD0: TP63.1 (1_1), U60.30 (GPIO17/U0RXD)
/Controller/SCL: R196.2, TP65.1 (1_1), U60.6 (GPIO3), U62.2 (SCL), U63.10 (SCL)
/Controller/SDA: R195.2, TP64.1 (1_1), U60.5 (GPIO2), U62.3 (SDA), U63.9 (SDA)
/Controller/STATUS: R203.1, U60.29 (GPIO23)
/Controller/TXD0: TP62.1 (1_1), U60.31 (GPIO16/U0TXD)
/Controller/USB_ESD_DN: R194.1, U61.4 (I/O2)
/Controller/USB_ESD_DP: R193.1, U61.6 (I/O1)
/Controller/USB_E_DN: C207.1, R194.2, U60.17 (GPIO12/USB_D-)
/Controller/USB_E_DP: C206.1, R193.2, U60.18 (GPIO13/USB_D+)
/DAC_HV: C203.1, R13.1, R212.2
/DAC_TH: C202.1, R85.2, R211.2
/Front End/HV_K: C50.1, D10.3 (K), R50.2
/Front End/LPF_OUT: C54.1, C55.1, R56.2, TP10.1 (1_1)
/Front End/PA_IN: C51.2, R51.1, U11.4 (IN+)
/Front End/TIA_IN: D10.1 (A), U10.15 (IN)
/HV_DIS: R34.2, U60.12 (GPIO0)
/HV_MON: C28.1, C197.1, R21.1, R32.2, R206.2, TP53.1 (1_1)
/LE_HYS: R83.2, R205.1
/LVDS_N: R180.2, U20.10 (OUT-), U50.7 (B)
/LVDS_P: R87.2, R180.1, U20.12 (OUT+), U50.6 (A)
/Monitor/RSSI_HOLD: C102.1, D30.1 (A), R103.1, TP32.1 (1_1), U30.5 (+)
/Power/5V_HVIN: C19.1, C20.1, L1.1, L2.2, R22.1, R29.2, U3.3 (VIN)
/Power/+5V: C1.1, C2.1, C9.1, C18.1, C29.1, L2.1, U1.1 (IN), U1.3 (EN), U4.1 (IN), U4.3 (EN), U5.5 (OUT)
/Power/BIAS: R28.1, R29.1, U3.7 (BIAS)
/Power/EN: Q3.3 (D), R22.2, R23.1, U3.1 (EN/UVLO), U6.2
/Power/FBX: C26.1, R8.1, R12.1, R14.2, R15.2, U3.9 (FBX)
/Power/HV_CLAMP: Q2.2 (E), R16.2, R19.1
/Power/HV_OUT: C25.1, Q1.3 (C), Q4.3, R11.2, R17.1, R20.1, R30.2
/Power/HV_PUMP: C6.2, D3.1 (K), D4.2 (A)
/Power/HV_RAW: C7.2, D4.1 (K), R30.1
/Power/HV_V1: C5.1, C7.1, D1.1 (K), R7.2
/Power/OVP_REF: R21.2, R45.1, U6.1
/Power/RT: R24.1, U3.10 (RT)
/Power/SS: C22.1, U3.11 (SS)
/Power/SYNC: R26.1, R27.1, TP2.1 (1_1), U3.12 (SYNC/MODE)
/Power/V3_FB: C12.2, R1.2, R2.1, U1.4 (FB)
/Power/VC: C24.1, R25.1, U3.8 (VC)
/RSSI: C198.1, R207.2, TP31.1 (1_1), TP52.1 (1_1), U30.6 (-), U30.7
/SDET_P: C55.2, C87.1, R59.1, TP11.1 (1_1), TP21.1 (1_1), U20.4 (IN+)
/SHDN_N: R81.1, U20.7 (SHDN), U60.13 (GPIO1)
/TIA_CTRL: JP10.2 (C), R57.2, R214.1, U10.2 (CTRL)
/TIA_TAP: D30.3 (K), R58.2
/USB_DN: J50.A7 (DN1), J50.B7 (DN2), U61.3 (I/O2)
/USB_DP: J50.A6 (DP1), J50.B6 (DP2), U61.1 (I/O1)
/VBUS: C33.1, D50.1, J50.A4 (VBUS), J50.A9 (VBUS), J50.B4 (VBUS), J50.B9 (VBUS), R35.1, U5.4 (IN), U61.5 (VBUS)
/VCM_REF: C101.1, R51.2, R59.2, R60.1, R84.2, R102.2, TP30.1 (1_1)
/VTH_MON: C199.1, R86.1, R208.2
GND: C1.2, C2.2, C5.2, C8.2, C9.2, C10.2, C11.2, C18.2, C19.2, C20.2, C21.2, C22.2, C23.2, C24.2, C25.2, C26.2, C27.2, C28.2, C29.2, C30.2, C31.2, C32.2, C33.2, C50.2, C52.2, C53.2, C54.2, C56.2, C57.2, C58.2, C59.2, C80.2, C81.2, C82.2, C83.2, C84.2, C100.2, C101.2, C102.2, C103.2, C180.2, C182.2, C183.2, C184.2, C185.2, C190.2, C191.1, C192.1, C194.2, C195.2, C196.1, C197.2, C198.2, C199.2, C200.1, C200.2, C201.2, C202.2, C203.2, C204.2, C206.2, C207.2, D2.2 (A), D10.2 (CASE), D50.2, D60.1 (K), H1.1, H2.1, H3.1, H4.1, J1.2, J50.A1 (GND), J50.A12 (GND), J50.B1 (GND), J50.B12 (GND), J50.S1 (SHIELD), J51.1, JP10.1 (A), Q3.2 (S), R2.2, R23.2, R24.2, R26.2, R27.2, R28.2, R37.2, R38.2, R45.2, R82.2, R101.2, R181.2, R184.2, R187.2, R189.2, R199.2, R209.2, RV1.3, SW60.1, SW61.1, TH1.2, TP54.1 (1_1), TP55.1 (1_1), U1.2 (GND), U3.17 (GND), U4.2 (GND), U5.1 (GND), U5.9 (EP), U6.3, U10.1 (GND), U10.3 (GND), U10.4 (GND), U10.6 (GND), U10.7 (GND), U10.12 (GND), U10.13 (TEST_SD_GND), U10.17 (PAD), U11.5 (VS-), U11.9 (EP), U20.3 (VEE), U20.5 (VEE), U20.9 (VEE), U20.11 (VEE), U20.13 (EP), U30.4 (V-), U50.5 (GND), U50.8 (EN4), U51.5 (GND), U51.10 (GND), U52.5 (GND), U52.10 (GND), U60.1 (GND), U60.2 (GND), U60.11 (GND), U60.14 (GND), U60.36 (GND), U60.37 (GND), U60.38 (GND), U60.39 (GND), U60.40 (GND), U60.41 (GND), U60.42 (GND), U60.43 (GND), U60.44 (GND), U60.45 (GND), U60.46 (GND), U60.47 (GND), U60.48 (GND), U60.49 (GND), U60.50 (GND), U60.51 (GND), U60.52 (GND), U60.53 (GND), U61.2 (GND), U62.10 (VSS), U63.1 (ADDR), U63.3 (GND), U64.2 (GND)
unnamed: C23.1, R25.2
unnamed: C27.1, R13.2, R14.1
unnamed: C53.1, R54.1, R60.2
unnamed: C87.2, R87.1
unnamed: C180.1, R182.2, R183.1
unnamed: C6.1, D1.2 (A), D2.1 (K), L1.2, U3.14 (SW2), U3.16 (SW1)
unnamed: D3.2 (A), R7.1
unnamed: D60.2 (A), R203.2
unnamed: J1.1, Q3.1 (G), R33.2, R34.1
unnamed: Q1.1 (B), Q4.2
unnamed: Q1.2 (E), Q2.1 (B), R16.1
unnamed: Q2.3 (C), Q4.1, R18.2
unnamed: R8.2, R9.1
unnamed: R9.2, R10.1
unnamed: R10.2, R11.1
unnamed: R12.2, TH1.1
unnamed: R15.1, RV1.2
unnamed: R17.2, R18.1
unnamed: R20.2, R32.1
unnamed: C21.1, U3.5 (INTVCC)
unnamed: R35.2, R36.1, U5.3 (EN/UVLO)
unnamed: R39.2, TP4.1 (1_1), U5.6 (FLT)
unnamed: R38.1, TP3.1 (1_1), U5.7 (ILM)
unnamed: R36.2, R37.1, U5.8 (OVLO)
unnamed: C32.1, U5.2 (dVdt)
unnamed: C51.1, R58.1, U10.8 (OUT)
unnamed: TP12.1 (1_1), U10.5 (OUTN)
unnamed: R53.2, U11.1 (FB)
unnamed: R53.1, R54.2, U11.3 (IN-)
unnamed: R56.1, U11.6 (OUT)
unnamed: C84.1, R84.1, R85.1, R86.2, TP20.1 (1_1), U20.6 (IN-)
unnamed: R82.1, R83.1, U20.8 (LE/HYS)
unnamed: C82.1, C83.1, R80.2, U20.1 (VCCO)
unnamed: C100.1, R100.2, R101.1, U30.3 (+)
unnamed: R102.1, U30.1, U30.2 (-)
unnamed: R204.1, U60.16 (GPIO7)
unnamed: R214.2, U60.26 (GPIO20)
unnamed: R199.1, U64.8 (RS)

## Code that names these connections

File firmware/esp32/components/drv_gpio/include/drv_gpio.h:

#pragma once
#include <stdbool.h>

/** Configure the GPIOs for boot (README s.4 step 1). SHDN_N and TIA_CTRL are
 *  left as plain inputs so the hardware pull-ups give comparator on and 20k.
 *  LED is an output (off). AUX is high-Z. DAC_LDAC (IO6) is an output held
 *  high (UDAC = 0 writes update their own channel). DAC_RDY belongs to
 *  drv_mcp4728 (mcp4728_init configures it). HV_DIS is NOT touched here
 *  (app_safety owns it). */
void drv_gpio_init(void);

/** TIA gain: true = 20k (pin released, pull-up), false = 5k (pin driven low,
 *  open-drain). */
void drv_gpio_tia_set(bool is_20k);
/** Current TIA pin level: true = 20k. */
bool drv_gpio_tia_get(void);

/** Comparator: true = on (SHDN_N released, pull-up), false = shutdown (driven
 *  low). Shutdown is not a guaranteed zero output (standing correction 11). */
void drv_gpio_comp_enable(bool on);
bool drv_gpio_comp_enabled(void);

void drv_gpio_led_set(bool on);

/** AUX (IO7): high impedance (default) or driven. */
void drv_gpio_aux_set_hiz(void);
void drv_gpio_aux_set(bool level);
/** Read the AUX pin level (for aux_in telemetry). */
bool drv_gpio_aux_read(void);

/** Read HV_DIS pad: true = high = HV disabled. */
bool drv_gpio_hv_dis_read(void);

/** SAFETY ONLY: write HV_DIS (true = disabled = pin high). Only app_safety
 *  may call this; nothing else in the firmware writes IO0. */
void drv_gpio_hv_dis_write(bool disabled);

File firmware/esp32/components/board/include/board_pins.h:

/* Board pin and constant map. Source: firmware/esp32/README.md s.1 (PROPOSED
 * hardware, docs/schematic/ sheets). Nothing here is measured. */
#pragma once

#define BOARD_PIN_HV_DIS      0   /* HIGH or Hi-Z = APD supply OFF. Written only by app_safety. */
#define BOARD_PIN_SHDN_N      1   /* TLV3605 shutdown, active low; pull-up keeps comparator on */
#define BOARD_PIN_I2C_SDA     2
#define BOARD_PIN_I2C_SCL     3
#define BOARD_PIN_CC1_SENSE   4   /* ADC1_CH4 */
#define BOARD_PIN_CC2_SENSE   5   /* ADC1_CH5 */
#define BOARD_PIN_DAC_LDAC    6
#define BOARD_PIN_AUX         7
#define BOARD_PIN_BOOT        9
#define BOARD_PIN_USB_DN      12
#define BOARD_PIN_USB_DP      13
#define BOARD_PIN_CAN_RX      18  /* swapped 2026-10-10 */
#define BOARD_PIN_CAN_TX      19
#define BOARD_PIN_TIA_CTRL    20  /* 1 = 20k, 0 = 5k; pull-up gives 20k */
#define BOARD_PIN_DAC_RDY     22  /* MCP4728 RDY/BSY, open drain */
#define BOARD_PIN_LED         23

#define BOARD_I2C_ADDR_MCP4728 0x60
#define BOARD_I2C_ADDR_ADS1115 0x48
/* 400 kHz fast mode: MCP4728 DS22187E p.1 (standard/fast/high-speed) and
 * ADS1115 SBAS444E (I2C timing table, fast mode) both support it. VERIFIED
 * by text search of docs/datasheets; the 4.7 k pull-up rise time at 400 kHz is
 * UNRESOLVED (not calculated). */
#define BOARD_I2C_FREQ_HZ      400000

#define BOARD_CAN_BITRATE      125000  /* protocol doc s.1 */

/* MCP4728 channel map (README s.1): index 0=A, 1=B, 2=C, 3=D */
#define BOARD_DAC_CH_TH        1   /* channel B = DAC_TH */
#define BOARD_DAC_CH_HV        2   /* channel C = DAC_HV */

/* ADS1115 channel map */
#define BOARD_ADC_AIN_HV_MON   0
#define BOARD_ADC_AIN_RSSI     1
#define BOARD_ADC_AIN_VTH_MON  2
#define BOARD_ADC_AIN_GND      3

#define BOARD_HV_MON_DIVIDER   101.0f   /* bias = AIN0 x 101 */

/* Safe DAC codes (README s.4 steps 4-5) */
#define BOARD_DAC_HV_SAFE_CODE 0xFFF    /* minimum bias */
#define BOARD_DAC_TH_ZERO_CODE 0x800    /* zero threshold offset */

/* Nominal bias per DAC_HV code, 14.95 mV (README s.4 step 9, calculated) */
#define BOARD_HV_V_PER_CODE    0.01495f
/* Bias at DAC_HV = 0xFFF with the trimmer at its default: "about 104 V"
 * (README s.1 DAC_HV row, calculated; PROPOSED, not measured). Used only for
 * the open-loop code bound (hv_gate.h, review finding 4). */
#define BOARD_HV_V_AT_SAFE_CODE 104.0f
